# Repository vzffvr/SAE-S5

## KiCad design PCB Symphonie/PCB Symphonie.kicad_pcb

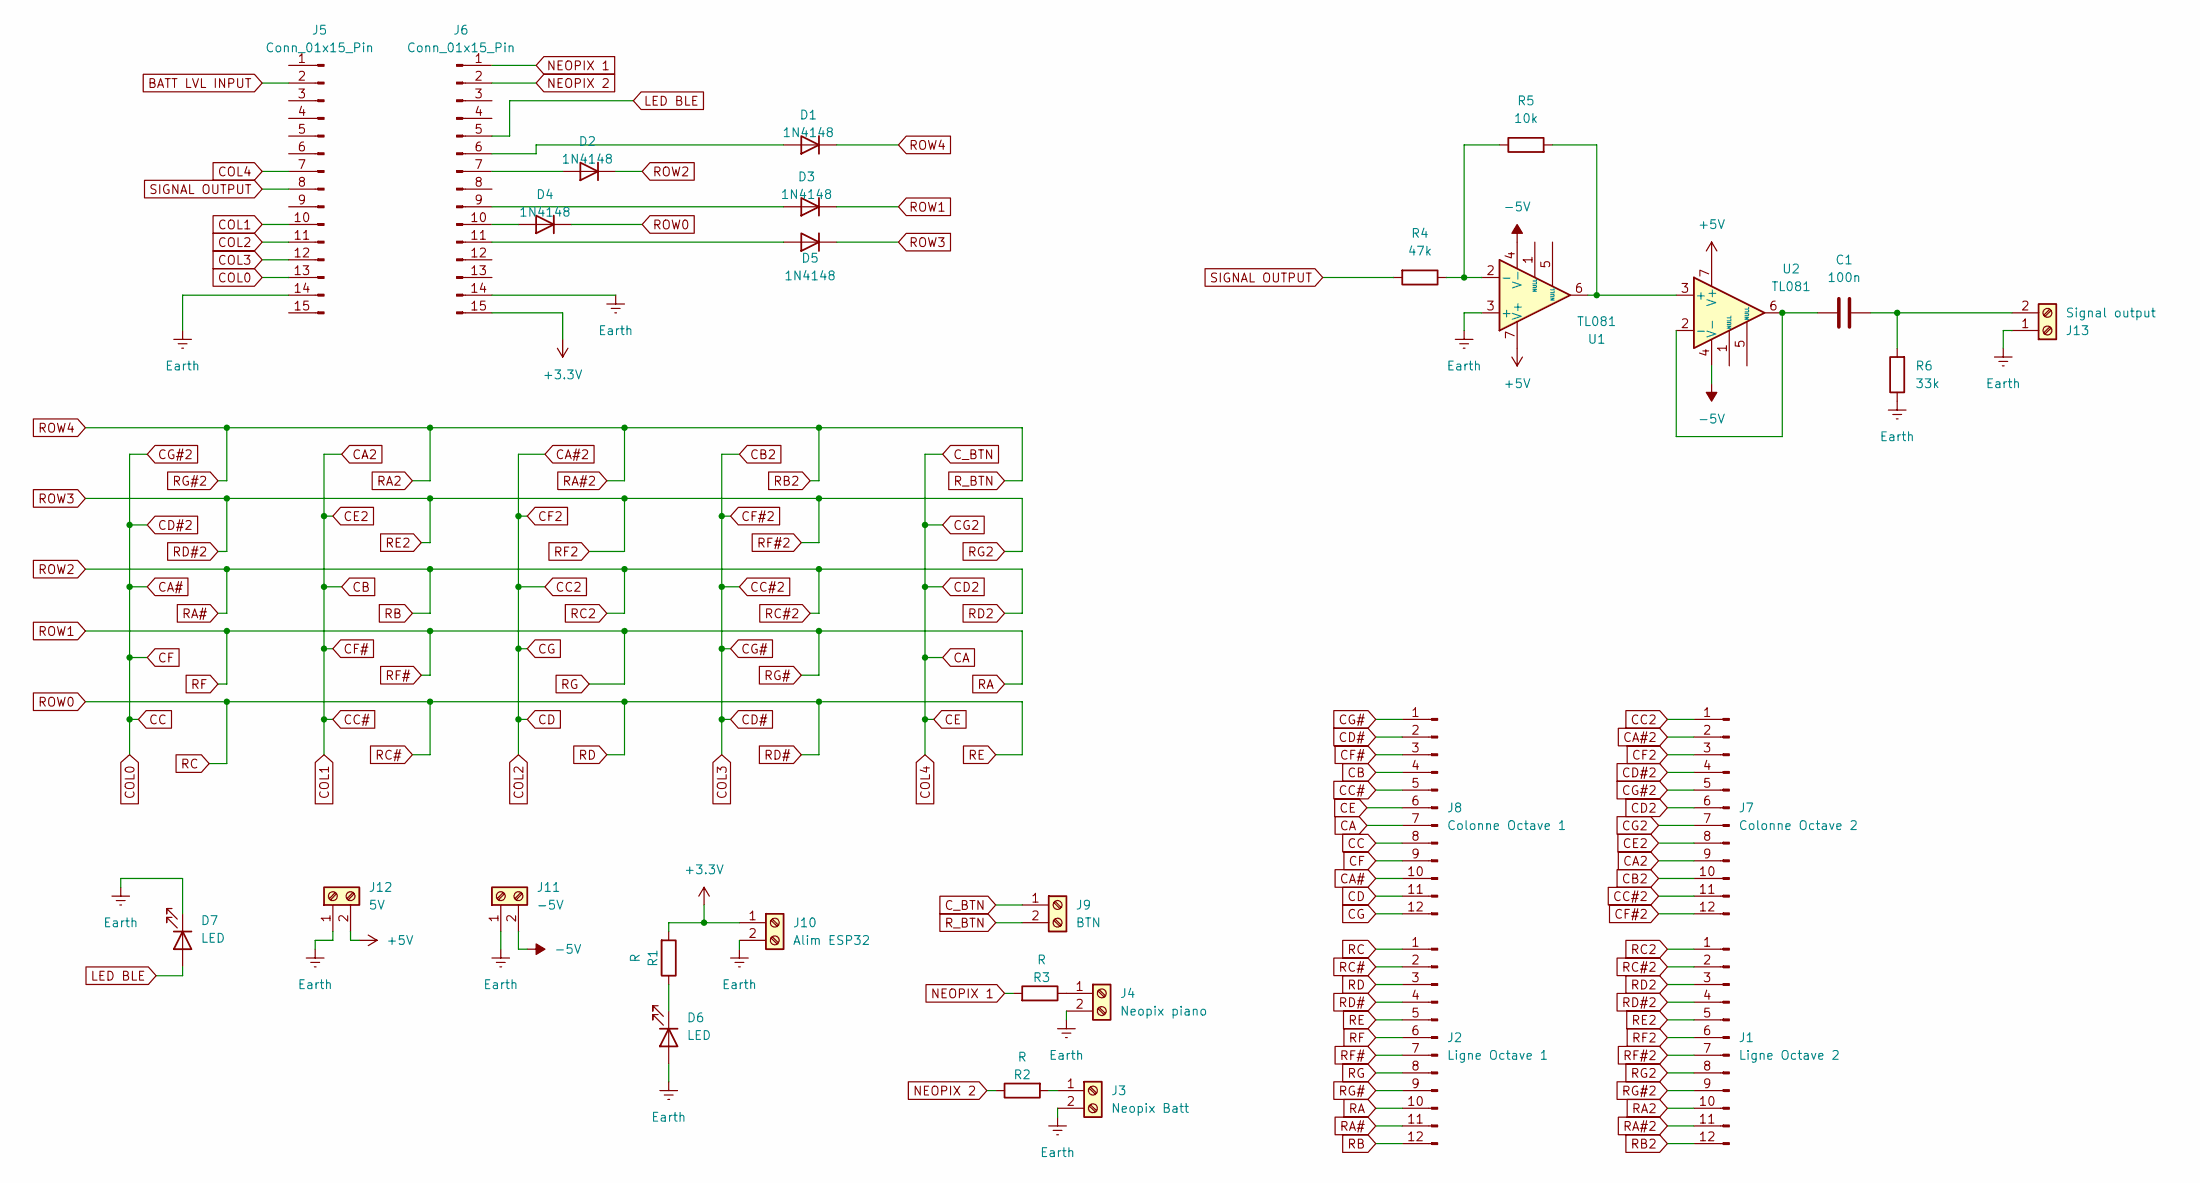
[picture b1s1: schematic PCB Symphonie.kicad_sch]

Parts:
C1: 100n; C_Rect_L7.0mm_W2.0mm_P5.00mm
D1, D2, D3, D4, D5: 1N4148; D_DO-35_SOD27_P7.62mm_Horizontal
D6, D7: LED; LED_D3.0mm
J1: Ligne Octave 2; PinSocket_1x12_P2.54mm_Vertical
J2: Ligne Octave 1; PinSocket_1x12_P2.54mm_Vertical
J3: Neopix Batt; TerminalBlock_MaiXu_MX126-5.0-02P_1x02_P5.00mm
J4: Neopix piano; TerminalBlock_MaiXu_MX126-5.0-02P_1x02_P5.00mm
J5, J6: Conn_01x15_Pin; PinHeader_1x15_P2.54mm_Vertical
J7: Colonne Octave 2; PinSocket_1x12_P2.54mm_Vertical
J8: Colonne Octave 1; PinSocket_1x12_P2.54mm_Vertical
J9: BTN; TerminalBlock_MaiXu_MX126-5.0-02P_1x02_P5.00mm
J10: Alim ESP32; TerminalBlock_MaiXu_MX126-5.0-02P_1x02_P5.00mm
J11: -5V; TerminalBlock_MaiXu_MX126-5.0-02P_1x02_P5.00mm
J12: 5V; TerminalBlock_MaiXu_MX126-5.0-02P_1x02_P5.00mm
J13: Signal output; TerminalBlock_MaiXu_MX126-5.0-02P_1x02_P5.00mm
R1, R2, R3: R; R_Axial_DIN0204_L3.6mm_D1.6mm_P7.62mm_Horizontal
R4: 47k; R_Axial_DIN0207_L6.3mm_D2.5mm_P7.62mm_Horizontal
R5: 10k; R_Axial_DIN0207_L6.3mm_D2.5mm_P7.62mm_Horizontal
R6: 33k; R_Axial_DIN0207_L6.3mm_D2.5mm_P7.62mm_Horizontal
U1, U2: TL081; DIP-8_W7.62mm_Socket

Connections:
+3.3V: J6.15, J10.1, R1.2
+5V: J12.2, U1.7 (V+), U2.7 (V+)
-5V: J11.2, U1.4 (V-), U2.4 (V-)
BATT LVL INPUT: J5.2
CA: J5.7, J7.6, J7.7, J8.6, J8.7, J9.1
CA2: J5.10, J7.8, J7.9, J8.3, J8.4, J8.5
CA#: J5.13, J7.4, J7.5, J8.8, J8.9, J8.10
CA#2: J5.11, J7.1, J7.2, J7.3, J8.11, J8.12
CB2: J5.12, J7.10, J7.11, J7.12, J8.1, J8.2
Earth: D6.2 (A), D7.1 (K), J3.2, J4.2, J5.14, J6.14, J10.2, J11.1, J12.1, J13.1, R6.1, U1.3 (+)
LED BLE: D7.2 (A), J6.5
NEOPIX 1: J6.1, R3.2
NEOPIX 2: J6.2, R2.1
unnamed: D1.2 (A), J6.6
unnamed: D2.2 (A), J6.7
unnamed: D3.2 (A), J6.9
unnamed: D4.2 (A), J6.10
unnamed: D5.2 (A), J6.11
unnamed: D6.1 (K), R1.1
unnamed: J3.1, R2.2
unnamed: J4.1, R3.1
unnamed: C1.2, J13.2, R6.2
unnamed: R4.1, R5.1, U1.2 (-)
unnamed: R5.2, U1.6, U2.3 (+)
unnamed: C1.1, U2.2 (-), U2.6
RA: D3.1 (K), J2.6, J2.7, J2.8, J2.9, J2.10
RA#: D2.1 (K), J1.1, J1.2, J1.3, J2.11, J2.12
RA#2: D1.1 (K), J1.9, J1.10, J1.11, J1.12, J9.2
RC: D4.1 (K), J2.1, J2.2, J2.3, J2.4, J2.5
RD#2: D5.1 (K), J1.4, J1.5, J1.6, J1.7, J1.8
SIGNAL OUTPUT: J5.8, R4.2

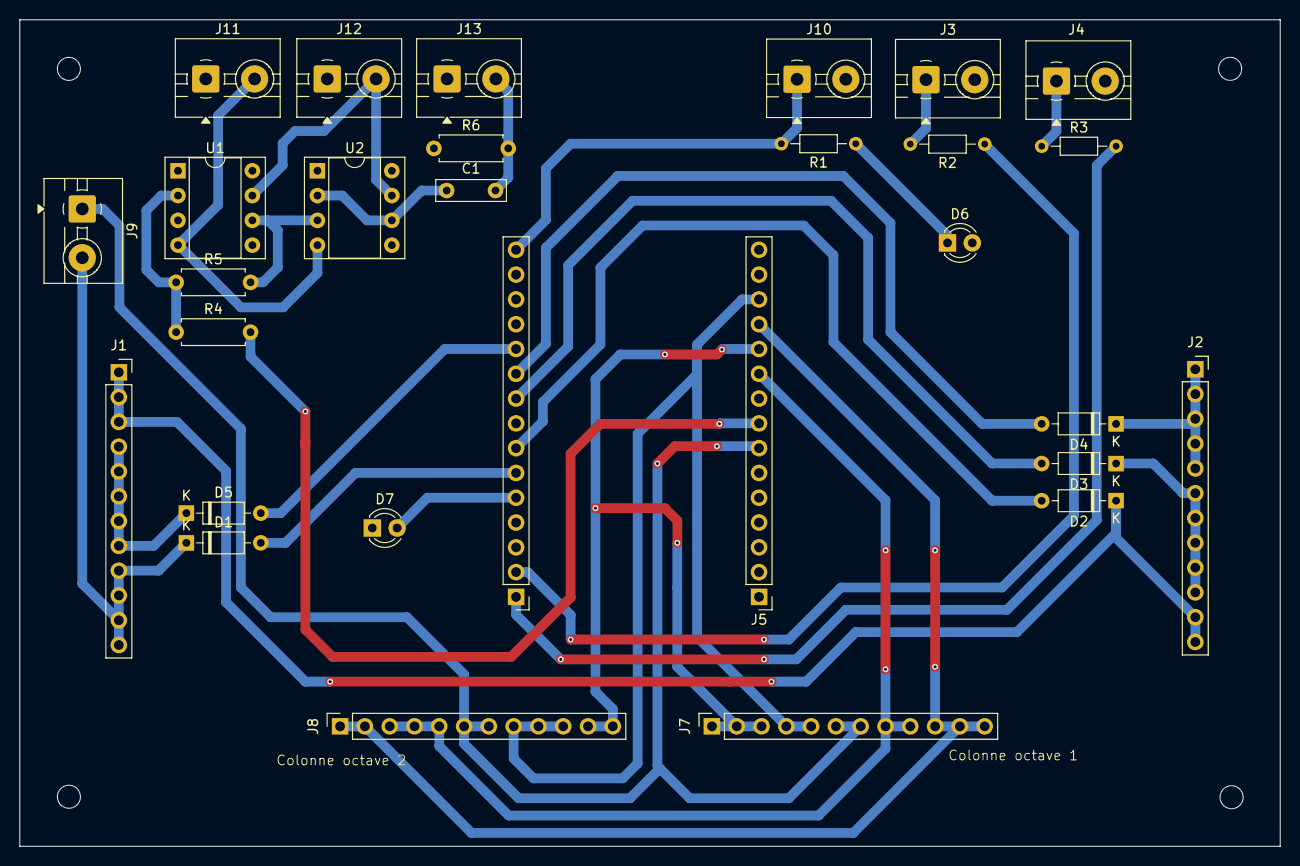
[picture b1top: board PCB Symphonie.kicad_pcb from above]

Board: 2 copper layers, 129.1 x 84.7 mm, 29 parts (0 on the bottom side), 30 nets.

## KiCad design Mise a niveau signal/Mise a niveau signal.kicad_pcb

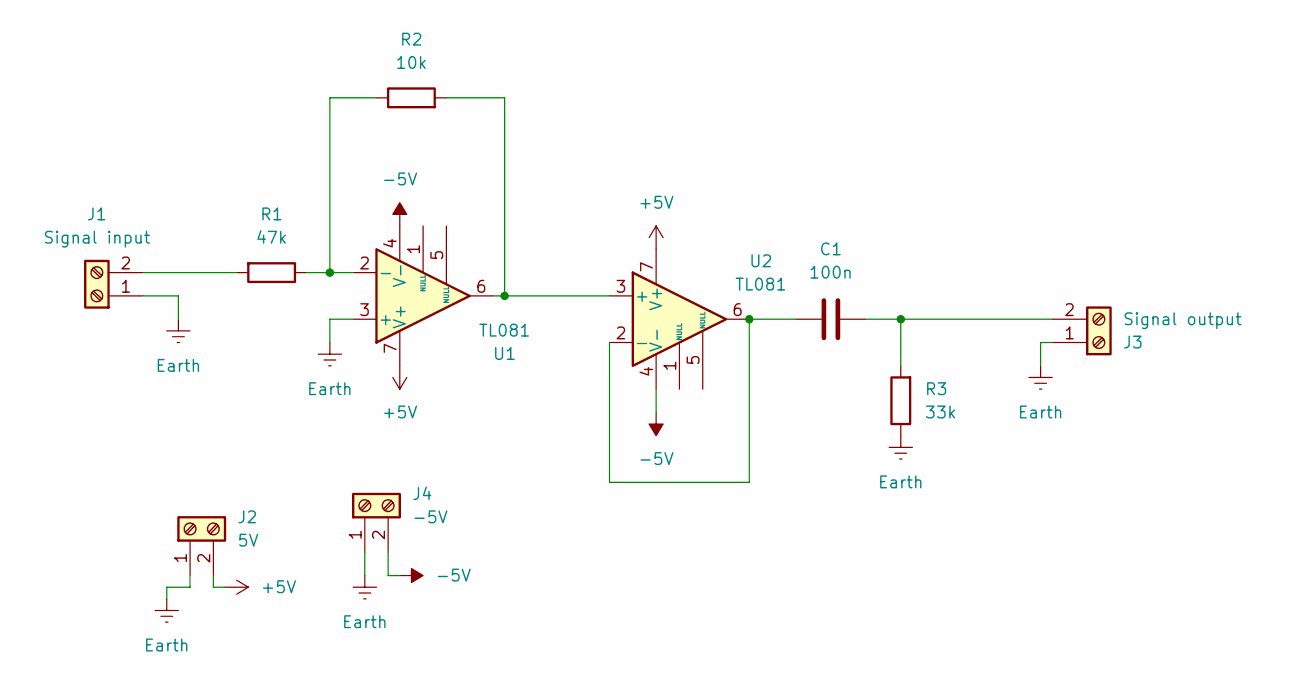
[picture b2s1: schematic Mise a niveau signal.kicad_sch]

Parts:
C1: 100n; C_Rect_L7.0mm_W2.0mm_P5.00mm
J1: Signal input; TerminalBlock_MaiXu_MX126-5.0-02P_1x02_P5.00mm
J2: 5V; TerminalBlock_MaiXu_MX126-5.0-02P_1x02_P5.00mm
J3: Signal output; TerminalBlock_MaiXu_MX126-5.0-02P_1x02_P5.00mm
J4: -5V; TerminalBlock_MaiXu_MX126-5.0-02P_1x02_P5.00mm
R1: 47k; R_Axial_DIN0207_L6.3mm_D2.5mm_P7.62mm_Horizontal
R2: 10k; R_Axial_DIN0207_L6.3mm_D2.5mm_P7.62mm_Horizontal
R3: 33k; R_Axial_DIN0207_L6.3mm_D2.5mm_P7.62mm_Horizontal
U1, U2: TL081; DIP-8_W7.62mm_Socket

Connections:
+5V: J2.2, U1.7 (V+), U2.7 (V+)
-5V: J4.2, U1.4 (V-), U2.4 (V-)
Earth: J1.1, J2.1, J3.1, J4.1, R3.1, U1.3 (+)
unnamed: J1.2, R1.2
unnamed: C1.2, J3.2, R3.2
unnamed: R1.1, R2.1, U1.2 (-)
unnamed: R2.2, U1.6, U2.3 (+)
unnamed: C1.1, U2.2 (-), U2.6

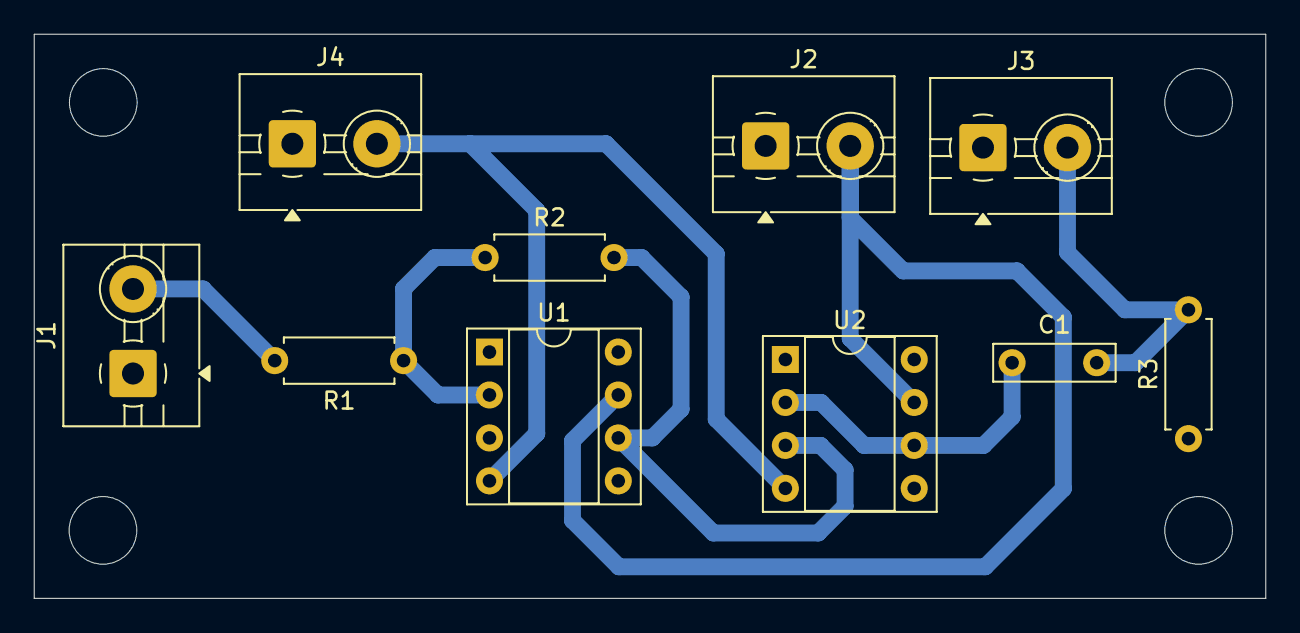
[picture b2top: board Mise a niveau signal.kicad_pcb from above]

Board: 2 copper layers, 72.8 x 33.4 mm, 10 parts (0 on the bottom side), 8 nets.

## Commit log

2024-09-18 Ajout App debut modif
2024-09-25 Debut analyse fonctionelle et cahier des charges
2024-09-26 Fin seance 29/09
2024-10-07 Reset pc
2024-10-20 Fin seance 18/08
    CDC mis a jour avec recommendation du prof, creation logo, Dossier planinfication a verifier gantt en cours analyse fonctionnelle et diapo en cours
2024-10-21 Fin seance21/10
    Mise en place logo Light and dark tehem
2024-10-27 MAJ cahier des charges et liste de composants
2024-10-27 Fin seance mercredi 23 octobre
    Modif app pas fini
2024-11-18 Fin, seance 18/11
    Implementation clavier fini maj colorpicker screen pour fit tout les ecrans,pb pour le mainscreen quand on change dp en fraction les button ne font plus la meme taille.
2024-11-22 Code matrice a tester
2024-11-26 Cablage ok PB de selection de ligne
    Si seulement 1 chiffre c est seulement que le 0 est effacé par la fonction serial. Si 2 alors col 0 ligne 2
2024-11-28 Marche pas 28/11
2024-11-28 R1 et 2 ok
    R0 nok a cause des leds. Ajout millis, res pulldown R voir shma
2024-12-17 v1 fini à imprimer
2025-01-27 code bleutooth
2025-01-30 30/01 BLE OK
    BLE Connection ok caracteristique et service trouve faire envoi
2025-01-31 Debut changement des pages MQTT -> BLE
2025-02-02 Connection et envoie OK
    Debut cahier de conception
    Connection et envoie BLE OK
    bouton reconnect OK
    Faire envoie touches piano
2025-02-05 Push pour cours 05/02
2025-02-06 Fin cours 06/02
    Faire connection genericUUID, Piano en jetpack compose
2025-02-06 Piano screen compose ok
    Faire envoi touche, envoi forme signal
    Investiguer sur librairie mozzi car signal chelou
2025-02-06 Piano screen complet
    Piano screen OK
    Config screen OK
2025-02-07 Recup toutes donnees ok Utilisable dans la loop
2025-02-08 PIANO screen ok
    GG
2025-02-08 Animation OK a tester
2025-02-09 Correction diff erreurs
    La plupart des anims sont ok,Faire reverse colorWipeCenter, colorWipeEdge.
    Inversion green et blue.
    Anim Suiveur marchje pas du tout
    Faire slider vitesse wipe
2025-02-15 Anim Siuiveur ok
2025-02-15 Multi touche
    Ajouter l'incrementation de la velocite
2025-02-16 Debut Schema Symphonie, Fin dossier de fab et nettoyage
2025-02-18 MAJ pcb
    ajout alim remplacement esp32 par connecteur
    Verifier taille condensateur (polarisation),
    demander a augustin res de puissances,
    replacer bouttons par piste et bornier
2025-02-18 MAJ Pin changement shematique verifier empreintes
2025-02-24 True multi button, correction pins pour row, et changmenet de nb max d appuie selon un define
    Peut etre cause du pb de signal bizarre
2025-02-25 Modif shema, Alim fait par simon
    Debut PCB
2025-02-26 maj pcb
2025-03-02 Routage bien avancer ajout mode auto
2025-03-02 fichiers stl à imprimer
2025-03-03 Creation diff fichier d'impressions, MAJ app pour selection channel, 3/4 dossier procedure et rapport de tests
2025-03-04 debut cours 4mars
2025-03-04 Fin cours 4mars
2025-03-05 Modif proc de test rapport de test a faire
    Correction bug retour en arriere melodie screeen
2025-03-06 Fin cours 6 mars
2025-03-06 Rapport de tests
2025-04-04 Maj de bcp de truc
2025-04-04 Documents
2025-04-27 Carte elec
2025-04-28 ajout STL
2025-04-30 Reglement probleme de non suppression du tableau des touche du tableau
2025-05-10 aethqh
